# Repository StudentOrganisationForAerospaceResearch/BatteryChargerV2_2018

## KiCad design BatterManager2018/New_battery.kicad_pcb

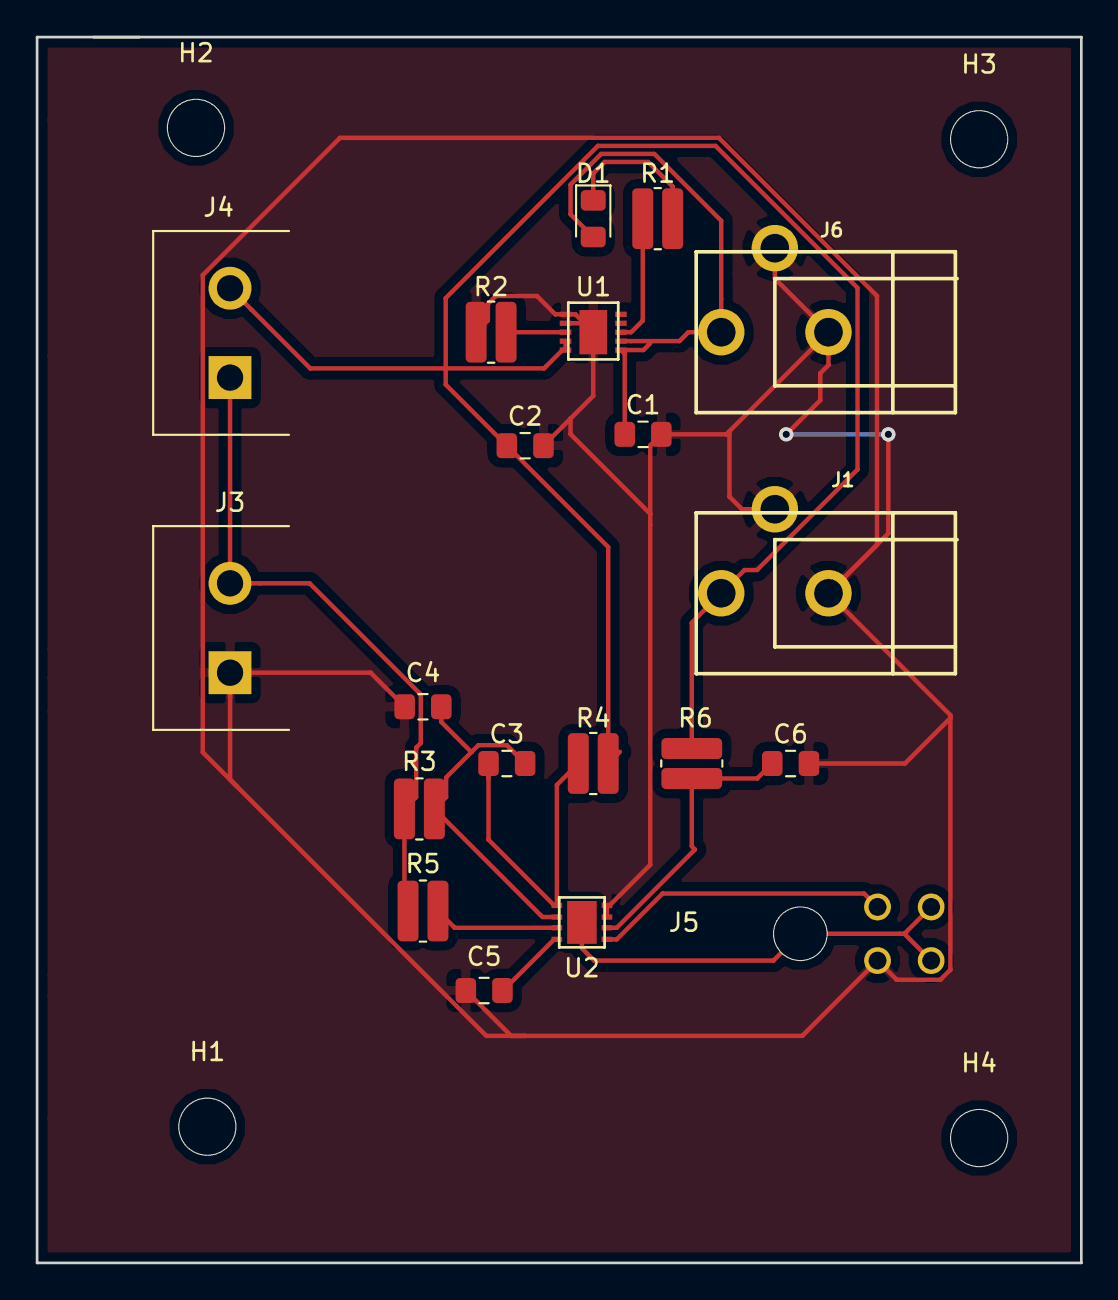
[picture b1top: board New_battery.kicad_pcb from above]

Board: 2 copper layers, 58.4 x 68.6 mm, 24 parts (0 on the bottom side), 13 nets.

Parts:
C1, C2: 4.7uf; C_0805_2012Metric_Pad1.15x1.40mm_HandSolder
C3, C4, C6: 0.1uf; C_0805_2012Metric_Pad1.15x1.40mm_HandSolder
C5: 0.33uf; C_0805_2012Metric_Pad1.15x1.40mm_HandSolder
D1: LED; LED_0805_2012Metric_Pad1.15x1.40mm_HandSolder
H1, H2, H3, H4: MountingHole; MountingHole_3.2mm_M3
J1, J6: Barrel_Jack; CUI_PJ-102A_2.5mm_DC_JACK
J3, J4: Screw_Terminal_01x02; TerminalBlock_5mm_2POS_ED2600
J5: Conn_01x02_Male; Molex_Micro-Fit_3.0_43045-0400_2x02_P3.00mm_Horizontal
R1: 1K; R_0612_1632Metric_Pad1.18x3.40mm_HandSolder
R2: 3K; R_0612_1632Metric_Pad1.18x3.40mm_HandSolder
R3: 260; R_0612_1632Metric_Pad1.18x3.40mm_HandSolder
R4: 160; R_0612_1632Metric_Pad1.18x3.40mm_HandSolder
R5, R6: 100; R_0612_1632Metric_Pad1.18x3.40mm_HandSolder
U1: MCP73213
U2: bq2920; bq29209_1

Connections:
GND: C1.2, C2.2, C4.2, C5.2, C6.2, J1.2, J1.3, J3.1, J5.1, J6.2, J6.3, R2.2, U1.9, U1.10, U1.11, U2.5, U2.6
unnamed: C3.1, R4.2, U2.1
unnamed: C3.2, C4.1, R3.2, U2.2
unnamed: C5.1, U2.4
unnamed: C6.1, R6.2, U2.7
unnamed: D1.1, R1.1
unnamed: J3.2, J4.1, R3.1, R5.1
unnamed: J5.2, U2.8
unnamed: R1.2, U1.3
unnamed: R2.1, U1.8
unnamed: R5.2, U2.3
VDD1: C2.1, J1.1, J4.2, R4.1, R6.1, U1.6, U1.7
VDD2: C1.1, D1.2, J6.1, U1.1, U1.2
